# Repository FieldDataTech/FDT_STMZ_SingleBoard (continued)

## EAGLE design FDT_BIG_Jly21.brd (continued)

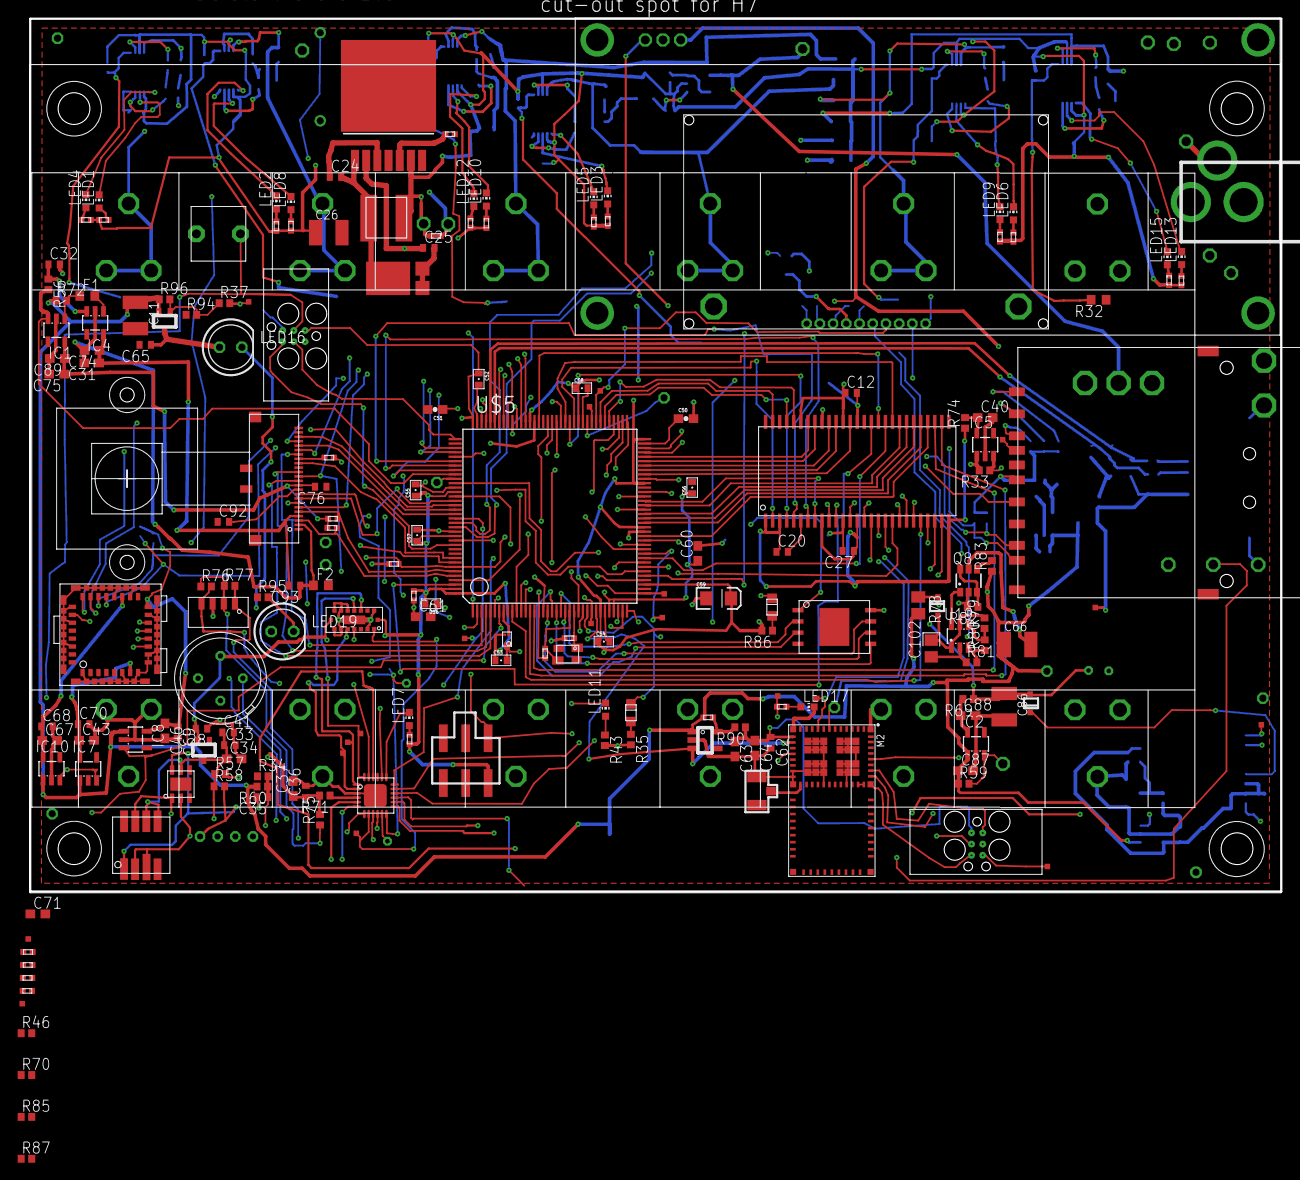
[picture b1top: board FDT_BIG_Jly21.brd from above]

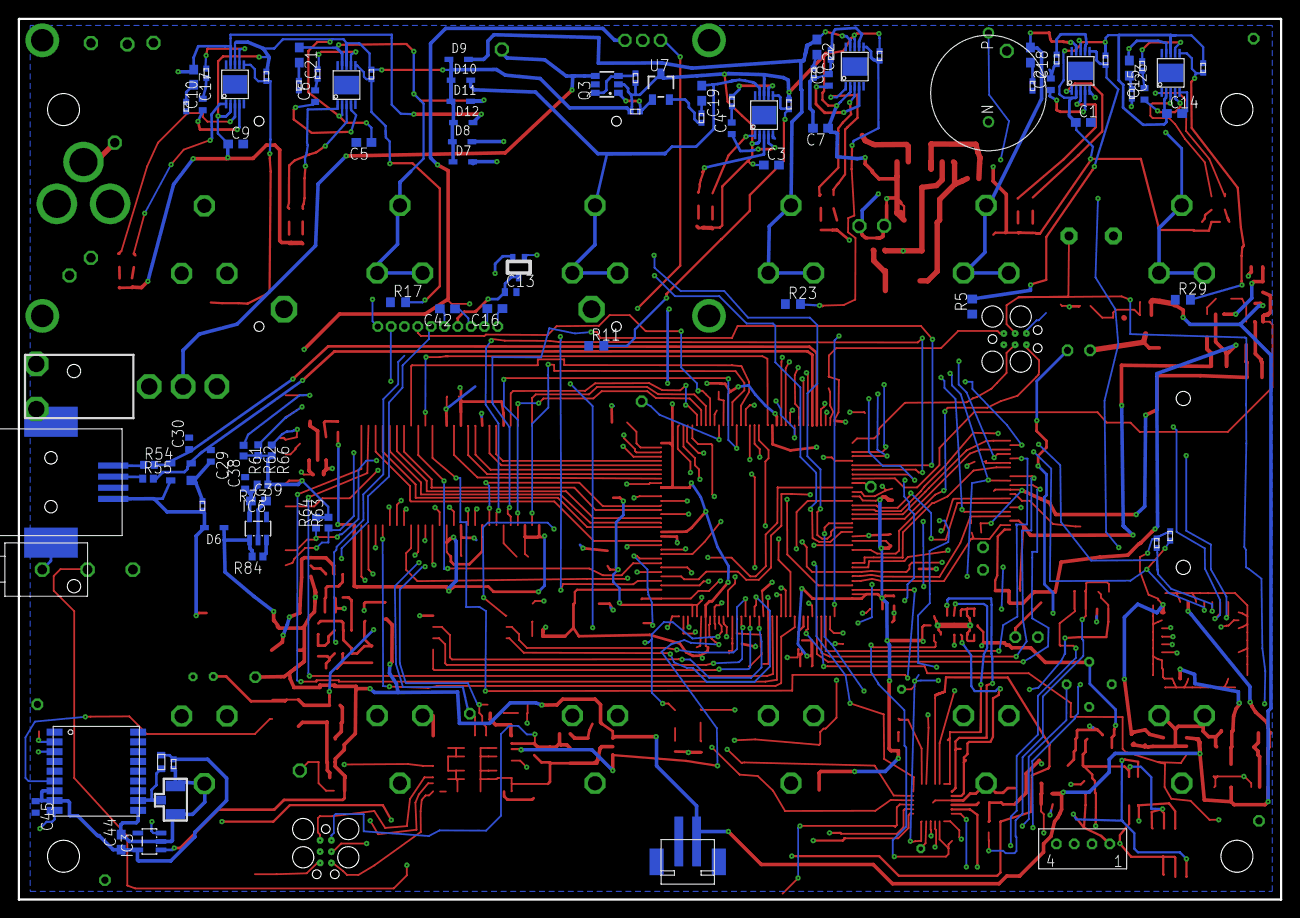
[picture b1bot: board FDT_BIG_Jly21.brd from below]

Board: 4 copper layers, 142.0 x 99.1 mm, 314 parts (93 on the bottom side), 253 nets.
